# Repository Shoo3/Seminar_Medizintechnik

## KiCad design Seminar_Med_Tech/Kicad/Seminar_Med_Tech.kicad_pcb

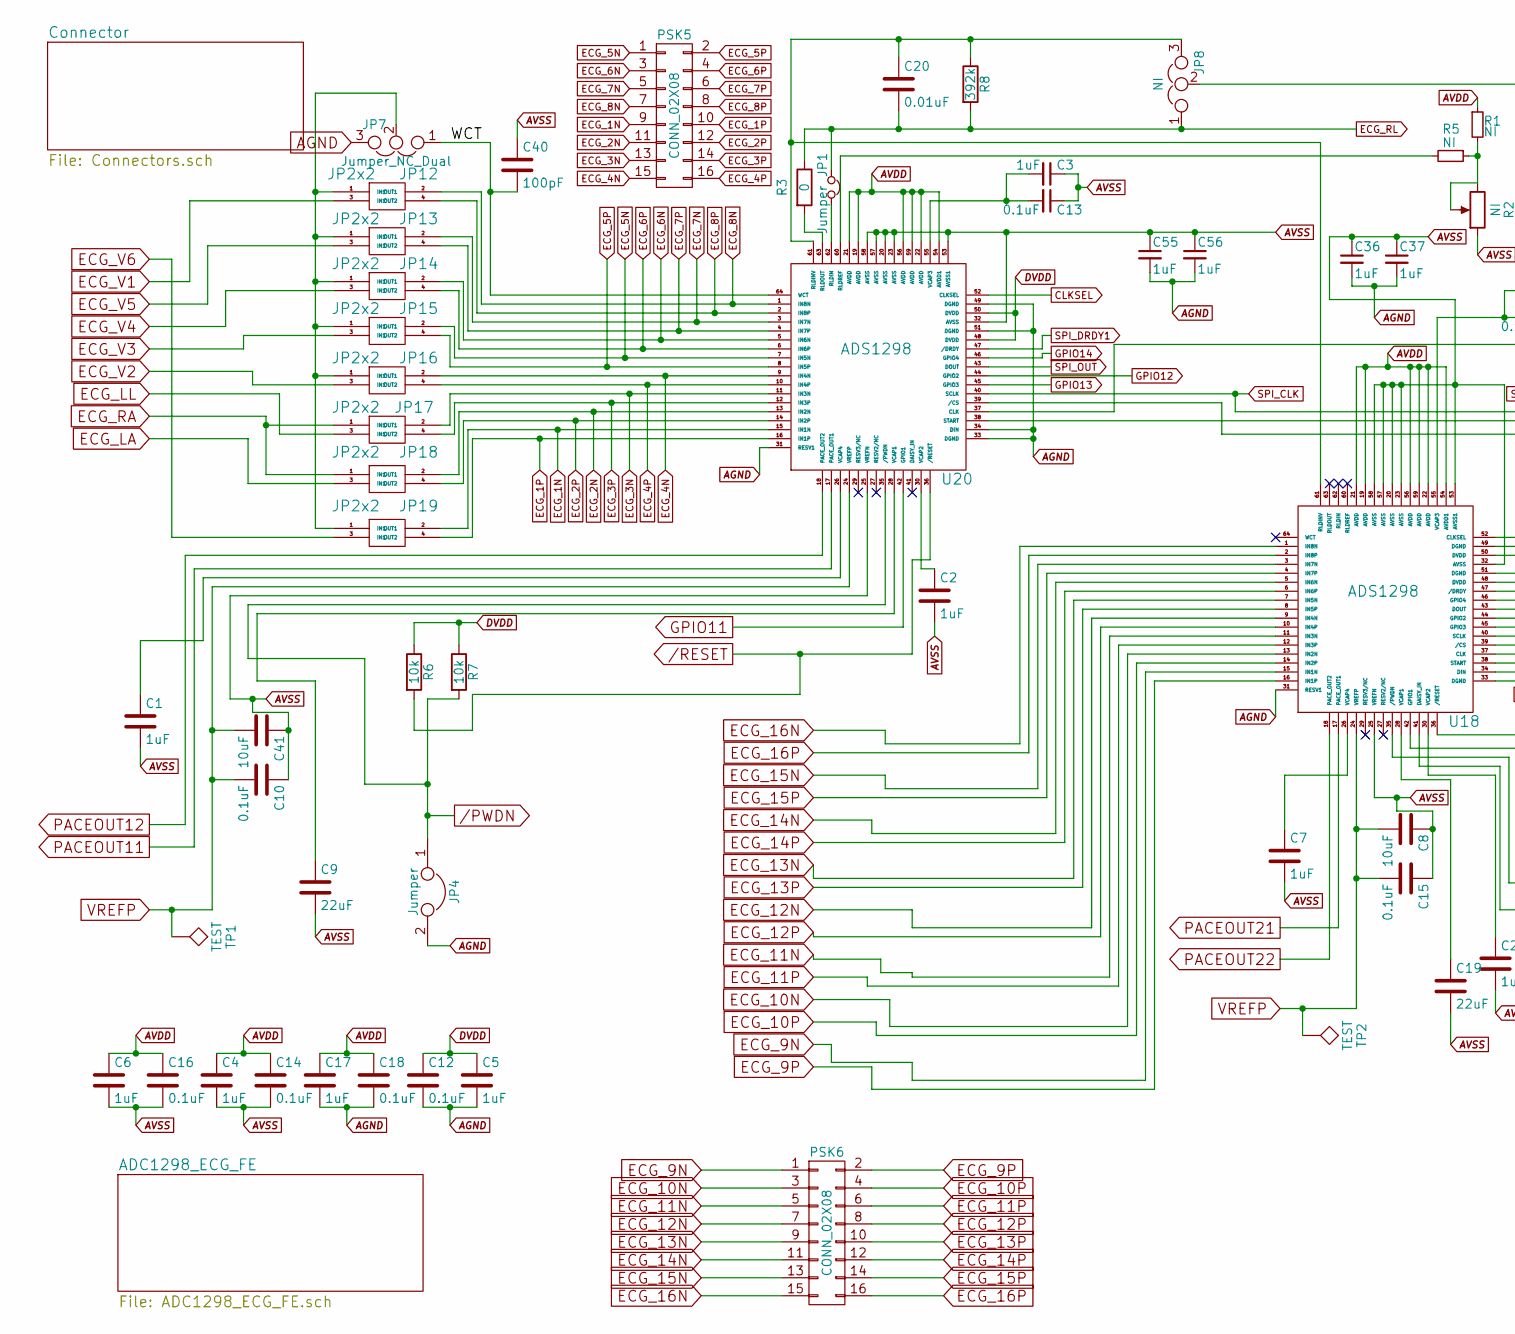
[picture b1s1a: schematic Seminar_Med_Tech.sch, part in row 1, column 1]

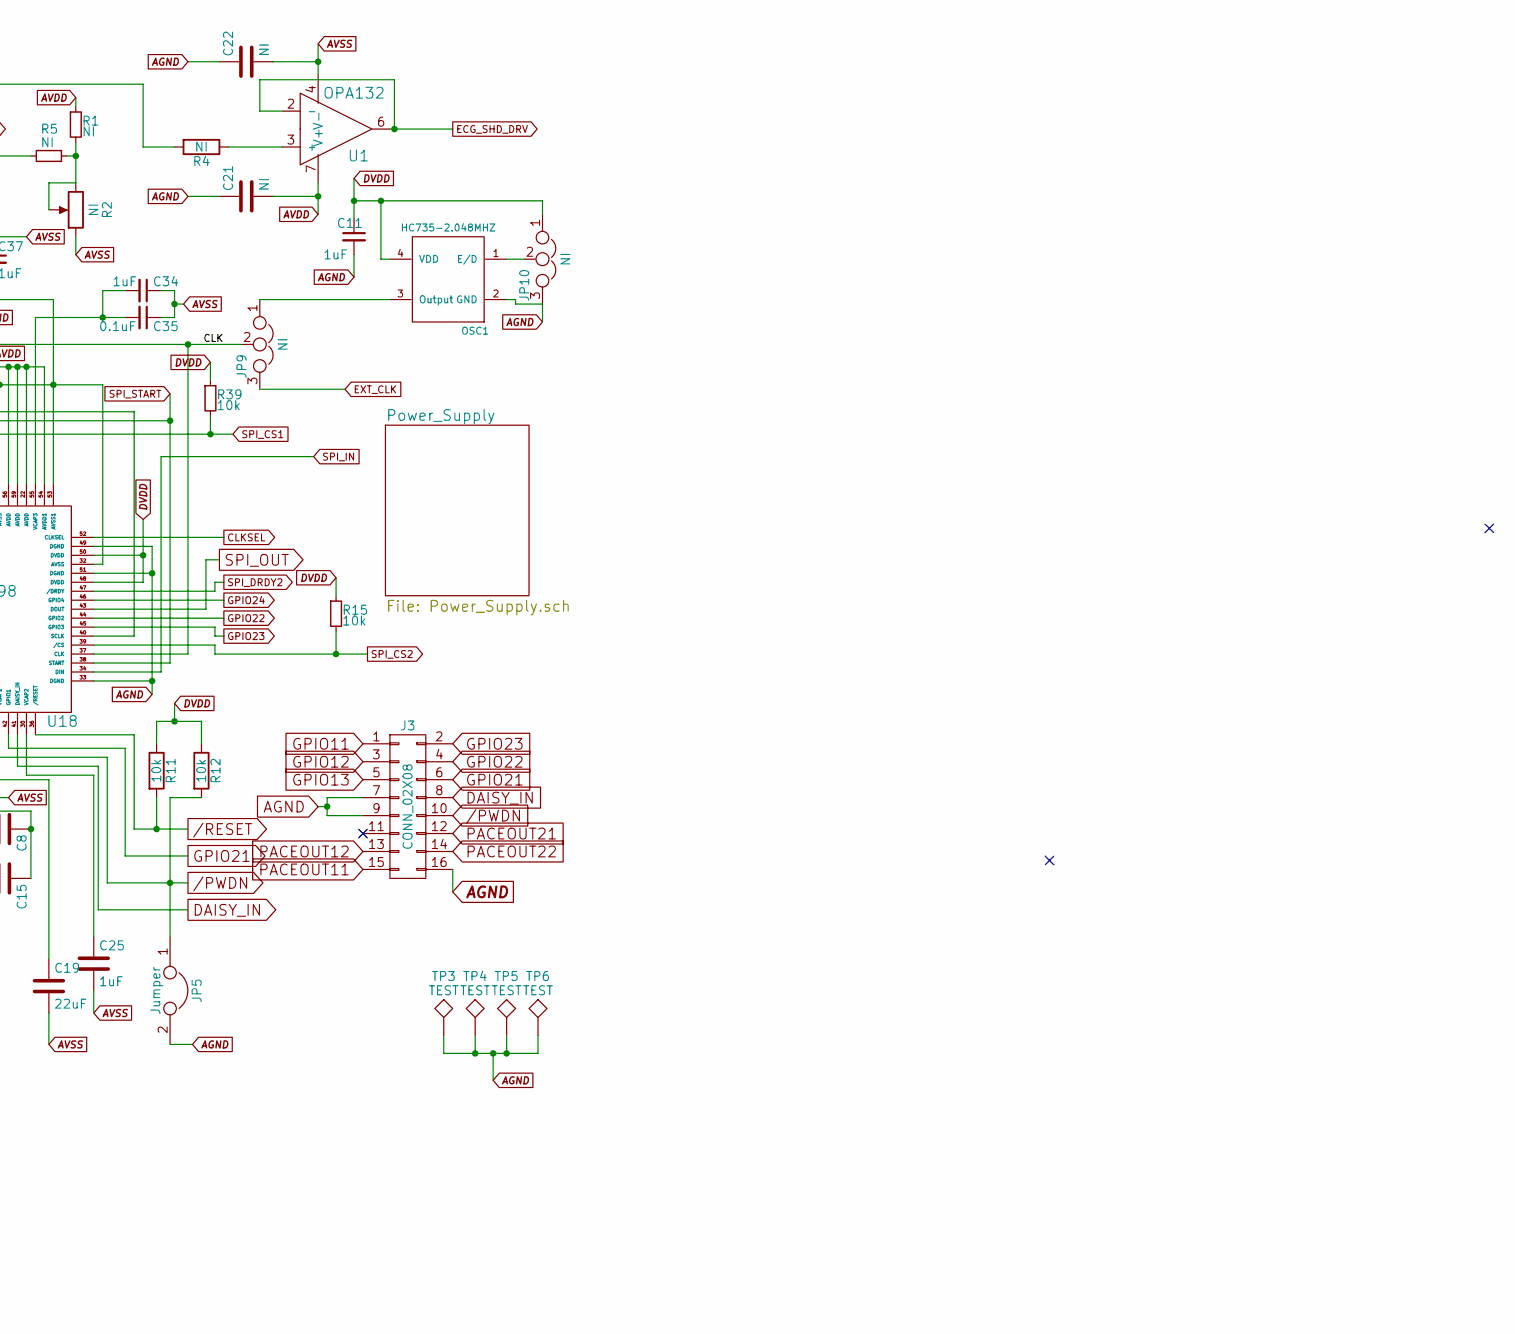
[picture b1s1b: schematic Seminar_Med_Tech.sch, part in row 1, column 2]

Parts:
C1, C2, C3, C4, C5, C6, C7, C11, C17, C25, C34, C36, C37, C55, C56: 1uF; C_1206_HandSoldering
C8, C41: 10uF; C_1206_HandSoldering
C9, C19: 22uF; C_1206_HandSoldering
C10, C12, C13, C14, C15, C16, C18, C35: 0.1uF; C_1206_HandSoldering
C20: 0.01uF; C_1206_HandSoldering
C21, C22: NI; C_1206_HandSoldering
C40: 100pF; C_1206_HandSoldering
J3: CONN_02X08; Pin_Header_Straight_2x08_Pitch2.54mm
JP1, JP4, JP5: Jumper; Jumper1x2
JP7: Jumper_NC_Dual; jumper1x3
JP8, JP9, JP10: NI; jumper1x3
JP12, JP13, JP14, JP15, JP16, JP17, JP18, JP19: JP2x2; Jumper2x2
OSC1: HC735-2.048MHZ; FXO-HC735
PSK5, PSK6: CONN_02X08; Pin_Header_Straight_2x08_Pitch2.54mm
R1, R4, R5: NI; R_0805_HandSoldering
R2: NI; Potentiometer_WirePads_Small
R3: 0; R_0805_HandSoldering
R6, R7, R11, R12, R15, R39: 10k; R_0805_HandSoldering
R8: 392k; R_0805_HandSoldering
TP1, TP2, TP3, TP4, TP5, TP6: TEST; Measurement_Point_Round-TH_Small
U1: OPA132
U18, U20: ADS1298

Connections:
/CLK: JP9.2, U18.37 (CLK), U20.37 (CLK)
/PWDN: J3.10, JP4.1, JP5.1, R7.2, R12.2, U18.35 (/PWDN), U20.35 (/PWDN)
/RESET: R6.2, R11.2, U18.36 (/RESET), U20.36 (/RESET); also elsewhere on the board
/WCT: C40.2, JP7.1, U20.64 (WCT)
AGND: C5.2, C11.2, C12.2, C17.2, C18.2, C21.1, C22.1, C36.2, C37.2, C55.2, C56.2, J3.7, J3.9, J3.16, JP4.2, JP5.2, JP7.3, JP10.3, OSC1.2 (GND), TP3.1, TP4.1, TP5.1, TP6.1, U18.31 (RESV1), U18.33 (DGND), U18.49 (DGND), U18.51 (DGND), U20.31 (RESV1), U20.33 (DGND), U20.34 (DIN), U20.49 (DGND), U20.51 (DGND); also elsewhere on the board
AVDD: C4.1, C6.1, C14.1, C16.1, C17.1, C18.1, C21.2, R1.1, U1.7 (V+), U18.19 (AVDD), U18.21 (AVDD), U18.22 (AVDD), U18.54 (AVDD1), U18.56 (AVDD), U18.59 (AVDD), U20.19 (AVDD), U20.21 (AVDD), U20.22 (AVDD), U20.54 (AVDD1), U20.56 (AVDD), U20.59 (AVDD); also elsewhere on the board
AVSS: C1.2, C2.2, C3.1, C4.2, C6.2, C7.2, C8.1, C9.2, C10.1, C13.1, C14.2, C15.1, C16.2, C19.2, C22.2, C25.2, C34.1, C35.1, C36.1, C37.1, C40.1, C41.1, C55.1, C56.1, R2.1, U1.4 (V-), U18.20 (AVSS), U18.23 (AVSS), U18.25 (VREFN), U18.32 (AVSS), U18.53 (AVSS1), U18.57 (AVSS), U18.58 (AVSS), U20.20 (AVSS), U20.23 (AVSS), U20.25 (VREFN), U20.32 (AVSS), U20.53 (AVSS1), U20.57 (AVSS), U20.58 (AVSS); also elsewhere on the board
CLKSEL: U18.52 (CLKSEL), U20.52 (CLKSEL); also elsewhere on the board
DAISY_IN: J3.8, U18.41 (DAISY_IN)
DVDD: C5.1, C11.1, C12.1, JP10.1, OSC1.4 (VDD), R6.1, R7.1, R11.1, R12.1, R15.1, R39.1, U18.48 (DVDD), U18.50 (DVDD), U20.48 (DVDD), U20.50 (DVDD); also elsewhere on the board
ECG_1N: JP19.2 (OUT1), PSK5.9, U20.15 (IN1N)
ECG_1P: JP19.4 (OUT2), PSK5.10, U20.16 (IN1P)
ECG_2N: JP18.2 (OUT1), PSK5.11, U20.13 (IN2N)
ECG_2P: JP18.4 (OUT2), PSK5.12, U20.14 (IN2P)
ECG_3N: JP17.2 (OUT1), PSK5.13, U20.11 (IN3N)
ECG_3P: JP17.4 (OUT2), PSK5.14, U20.12 (IN3P)
ECG_4N: JP16.2 (OUT1), PSK5.15, U20.9 (IN4N)
ECG_4P: JP16.4 (OUT2), PSK5.16, U20.10 (IN4P)
ECG_5N: JP15.2 (OUT1), PSK5.1, U20.7 (IN5N)
ECG_5P: JP15.4 (OUT2), PSK5.2, U20.8 (IN5P)
ECG_6N: JP14.2 (OUT1), PSK5.3, U20.5 (IN6N)
ECG_6P: JP14.4 (OUT2), PSK5.4, U20.6 (IN6P)
ECG_7N: JP13.2 (OUT1), PSK5.5, U20.3 (IN7N)
ECG_7P: JP13.4 (OUT2), PSK5.6, U20.4 (IN7P)
ECG_8N: JP12.2 (OUT1), PSK5.7, U20.1 (IN8N)
ECG_8P: JP12.4 (OUT2), PSK5.8, U20.2 (IN8P)
ECG_9N: PSK6.1, U18.15 (IN1N)
ECG_9P: PSK6.2, U18.16 (IN1P)
ECG_10N: PSK6.3, U18.13 (IN2N)
ECG_10P: PSK6.4, U18.14 (IN2P)
ECG_11N: PSK6.5, U18.11 (IN3N)
ECG_11P: PSK6.6, U18.12 (IN3P)
ECG_12N: PSK6.7, U18.9 (IN4N)
ECG_12P: PSK6.8, U18.10 (IN4P)
ECG_13N: PSK6.9, U18.7 (IN5N)
ECG_13P: PSK6.10, U18.8 (IN5P)
ECG_14N: PSK6.11, U18.5 (IN6N)
ECG_14P: PSK6.12, U18.6 (IN6P)
ECG_15N: PSK6.13, U18.3 (IN7N)
ECG_15P: PSK6.14, U18.4 (IN7P)
ECG_16N: PSK6.15, U18.1 (IN8N)
ECG_16P: PSK6.16, U18.2 (IN8P)
ECG_LA: JP18.3 (IN1); also elsewhere on the board
ECG_LL: JP17.3 (IN1); also elsewhere on the board
ECG_RA: JP17.1 (IN1), JP18.1 (IN1); also elsewhere on the board
ECG_RL: C20.2, JP1.1, JP8.1, R3.1, R8.2; also elsewhere on the board
ECG_SHD_DRV: U1.2 (-), U1.6; also elsewhere on the board
ECG_V1: JP12.3 (IN1); also elsewhere on the board
ECG_V2: JP16.3 (IN1); also elsewhere on the board
ECG_V3: JP15.3 (IN1); also elsewhere on the board
ECG_V4: JP14.3 (IN1); also elsewhere on the board
ECG_V5: JP13.3 (IN1); also elsewhere on the board
ECG_V6: JP19.3 (IN1); also elsewhere on the board
EXT_CLK: JP9.3; also elsewhere on the board
GPIO11: J3.1, U20.42 (GPIO1)
GPIO12: J3.3, U20.44 (GPIO2)
GPIO13: J3.5, U20.45 (GPIO3)
GPIO14: U20.46 (GPIO4); also elsewhere on the board
GPIO21: J3.6, U18.42 (GPIO1)
GPIO22: J3.4, U18.44 (GPIO2)
GPIO23: J3.2, U18.45 (GPIO3)
GPIO24: U18.46 (GPIO4); also elsewhere on the board
unnamed: C1.1, U20.26 (VCAP4)
unnamed: C2.1, U20.30 (VCAP2)
unnamed: C7.1, U18.26 (VCAP4)
unnamed: C9.1, U20.28 (VCAP1)
unnamed: C3.2, C13.2, U20.55 (VCAP3)
unnamed: C19.1, U18.28 (VCAP1)
unnamed: C20.1, JP8.3, R8.1, U18.61 (RLDINV), U20.61 (RLDINV)
unnamed: C25.1, U18.30 (VCAP2)
unnamed: C34.2, C35.2, U18.55 (VCAP3)
unnamed: JP1.2, U20.62 (RLDIN)
unnamed: JP8.2, R4.2
unnamed: JP9.1, OSC1.3 (Output)
unnamed: JP10.2, OSC1.1 (E/D)
unnamed: JP7.2, JP12.1 (IN1), JP13.1 (IN1), JP14.1 (IN1), JP15.1 (IN1), JP16.1 (IN1), JP19.1 (IN1)
unnamed: R1.2, R2.2, R2.3, R5.1
unnamed: R3.2, U20.63 (RLDOUT)
unnamed: R4.1, U1.3 (+)
unnamed: R5.2, U20.60 (RLDREF)
PACEOUT11: J3.15, U20.17 (PACE_OUT1)
PACEOUT12: J3.13, U20.18 (PACE_OUT2)
PACEOUT21: J3.12, U18.17 (PACE_OUT1)
PACEOUT22: J3.14, U18.18 (PACE_OUT2)
SPI_CLK: U18.40 (SCLK), U20.40 (SCLK); also elsewhere on the board
SPI_CS1: R39.2, U20.39 (/CS); also elsewhere on the board
SPI_CS2: R15.2, U18.39 (/CS); also elsewhere on the board
SPI_DRDY1: U20.47 (/DRDY); also elsewhere on the board
SPI_DRDY2: U18.47 (/DRDY); also elsewhere on the board
SPI_IN: U18.34 (DIN); also elsewhere on the board
SPI_OUT: U18.43 (DOUT), U20.43 (DOUT); also elsewhere on the board
SPI_START: U18.38 (START), U20.38 (START); also elsewhere on the board
VREFP: C8.2, C10.2, C15.2, C41.2, TP1.1, TP2.1, U18.24 (VREFP), U20.24 (VREFP)

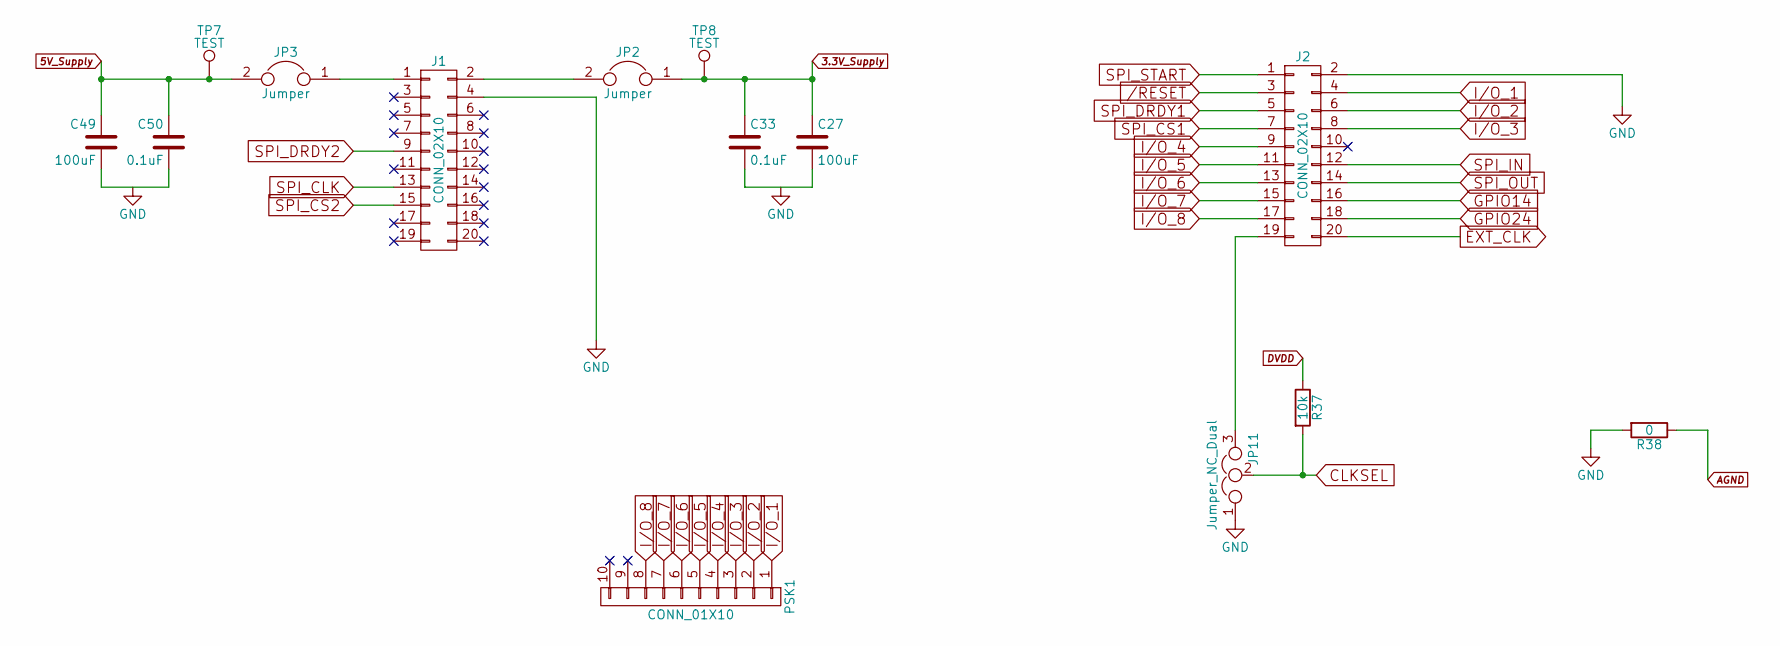
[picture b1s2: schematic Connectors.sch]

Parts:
C27, C49: 100uF; C_1206_HandSoldering
C33, C50: 0.1uF; C_1206_HandSoldering
J1, J2: CONN_02X10; Pin_Header_Straight_2x10_Pitch2.54mm
JP2, JP3: Jumper; Jumper1x2
JP11: Jumper_NC_Dual; jumper1x3
PSK1: CONN_01X10; Pin_Header_Straight_1x10_Pitch2.54mm
R37: 10k; R_0805_HandSoldering
R38: 0; R_0805_HandSoldering
TP7, TP8: TEST; Measurement_Point_Round-TH_Small

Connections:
3.3V_Supply: C27.1, C33.1, JP2.1, TP8.1; also elsewhere on the board
5V_Supply: C49.1, C50.1, JP3.2, TP7.1; also elsewhere on the board
/RESET: J2.3; also elsewhere on the board
AGND: R38.1; also elsewhere on the board
CLKSEL: JP11.2, R37.2; also elsewhere on the board
DVDD: R37.1; also elsewhere on the board
EXT_CLK: J2.20; also elsewhere on the board
GPIO14: J2.16; also elsewhere on the board
GPIO24: J2.18; also elsewhere on the board
I/O_1: J2.4, PSK1.1
I/O_2: J2.6, PSK1.2
I/O_3: J2.8, PSK1.3
I/O_4: J2.9, PSK1.4
I/O_5: J2.11, PSK1.5
I/O_6: J2.13, PSK1.6
I/O_7: J2.15, PSK1.7
I/O_8: J2.17, PSK1.8
unnamed: J2.19, JP11.3
SPI_CLK: J1.13; also elsewhere on the board
SPI_CS1: J2.7; also elsewhere on the board
SPI_CS2: J1.15; also elsewhere on the board
SPI_DRDY1: J2.5; also elsewhere on the board
SPI_DRDY2: J1.9; also elsewhere on the board
SPI_IN: J2.12; also elsewhere on the board
SPI_OUT: J2.14; also elsewhere on the board
SPI_START: J2.1; also elsewhere on the board

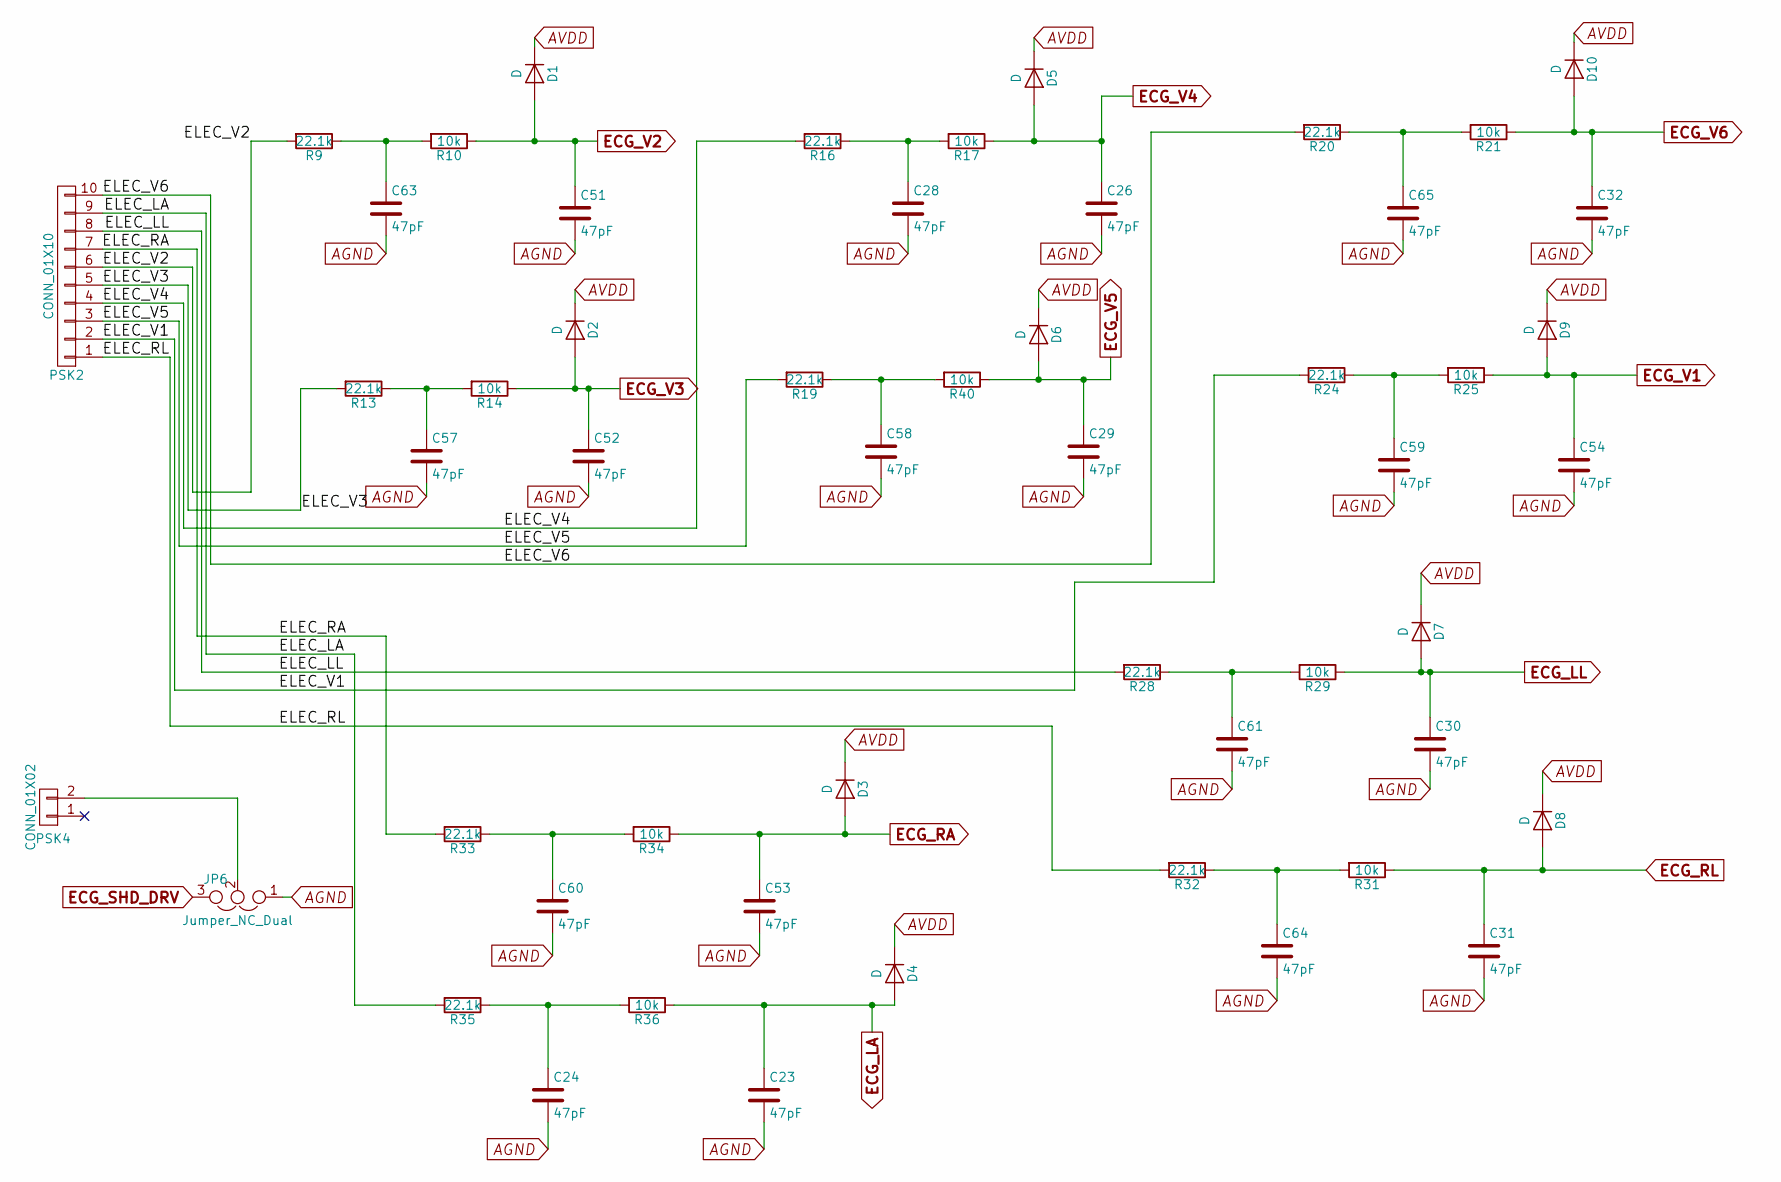
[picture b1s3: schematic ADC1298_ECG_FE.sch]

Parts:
C23, C24, C26, C28, C29, C30, C31, C32, C51, C52, C53, C54, C57, C58, C59, C60, C61, C63, C64, C65: 47pF; C_1206_HandSoldering
D1, D2, D3, D4, D5, D6, D7, D8, D9, D10: D; D_SOD-123
JP6: Jumper_NC_Dual; jumper1x3
PSK2: CONN_01X10; Pin_Header_Straight_1x10_Pitch2.54mm
PSK4: CONN_01X02; Pin_Header_Straight_1x02_Pitch2.54mm
R9, R13, R16, R19, R20, R24, R28, R32, R33, R35: 22.1k; R_0805_HandSoldering
R10, R14, R17, R21, R25, R29, R31, R34, R36, R40: 10k; R_0805_HandSoldering

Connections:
/ADC1298_ECG_FE/ELEC_LA: PSK2.9, R35.2
/ADC1298_ECG_FE/ELEC_LL: PSK2.8, R28.2
/ADC1298_ECG_FE/ELEC_RA: PSK2.7, R33.2
/ADC1298_ECG_FE/ELEC_RL: PSK2.1, R32.2
/ADC1298_ECG_FE/ELEC_V1: PSK2.2, R24.2
/ADC1298_ECG_FE/ELEC_V2: PSK2.6, R9.2
/ADC1298_ECG_FE/ELEC_V3: PSK2.5, R13.2
/ADC1298_ECG_FE/ELEC_V4: PSK2.4, R16.2
/ADC1298_ECG_FE/ELEC_V5: PSK2.3, R19.2
/ADC1298_ECG_FE/ELEC_V6: PSK2.10, R20.2
AGND: C23.2, C24.2, C26.2, C28.2, C29.2, C30.2, C31.2, C32.2, C51.2, C52.2, C53.2, C54.2, C57.2, C58.2, C59.2, C60.2, C61.2, C63.2, C64.2, C65.2, JP6.1; also elsewhere on the board
AVDD: D1.1 (K), D2.1 (K), D3.1 (K), D4.1 (K), D5.1 (K), D6.1 (K), D7.1 (K), D8.1 (K), D9.1 (K), D10.1 (K); also elsewhere on the board
ECG_LA: C23.1, D4.2 (A), R36.1; also elsewhere on the board
ECG_LL: C30.1, D7.2 (A), R29.1; also elsewhere on the board
ECG_RA: C53.1, D3.2 (A), R34.1; also elsewhere on the board
ECG_RL: C31.1, D8.2 (A), R31.1; also elsewhere on the board
ECG_SHD_DRV: JP6.3; also elsewhere on the board
ECG_V1: C54.1, D9.2 (A), R25.1; also elsewhere on the board
ECG_V2: C51.1, D1.2 (A), R10.1; also elsewhere on the board
ECG_V3: C52.1, D2.2 (A), R14.1; also elsewhere on the board
ECG_V4: C26.1, D5.2 (A), R17.1; also elsewhere on the board
ECG_V5: C29.1, D6.2 (A), R40.1; also elsewhere on the board
ECG_V6: C32.1, D10.2 (A), R21.1; also elsewhere on the board
unnamed: C24.1, R35.1, R36.2
unnamed: C28.1, R16.1, R17.2
unnamed: C57.1, R13.1, R14.2
unnamed: C58.1, R19.1, R40.2
unnamed: C59.1, R24.1, R25.2
unnamed: C60.1, R33.1, R34.2
unnamed: C61.1, R28.1, R29.2
unnamed: C63.1, R9.1, R10.2
unnamed: C64.1, R31.2, R32.1
unnamed: C65.1, R20.1, R21.2
unnamed: JP6.2, PSK4.2

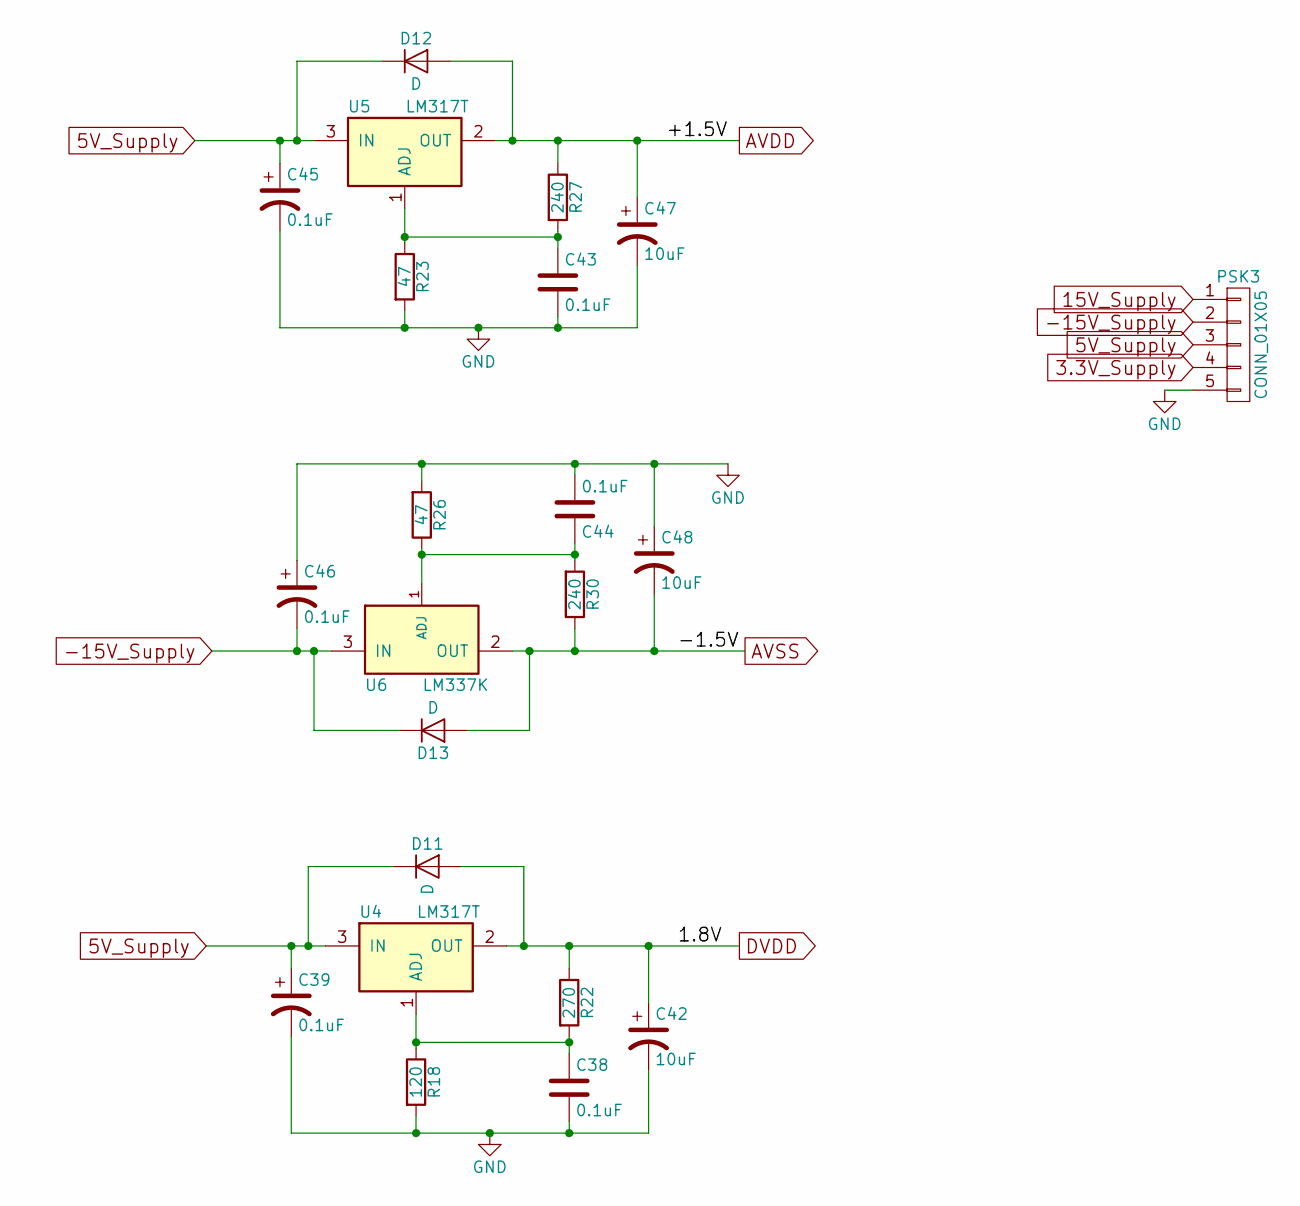
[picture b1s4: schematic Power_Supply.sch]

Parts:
C38, C43, C44: 0.1uF; C_1206_HandSoldering
C39, C45, C46: 0.1uF; 4mmx5,5mmSMDElec
C42, C47, C48: 10uF; 4mmx5,5mmSMDElec10uf
D11, D12, D13: D; D_SOD-123
PSK3: CONN_01X05; Pin_Header_Straight_1x05_Pitch2.54mm
R18: 120; R_0805_HandSoldering
R22: 270; R_0805_HandSoldering
R23, R26: 47; R_0805_HandSoldering
R27, R30: 240; R_0805_HandSoldering
U4, U5: LM317T; LM317
U6: LM337K; LM317

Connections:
3.3V_Supply: PSK3.4; also elsewhere on the board
5V_Supply: C39.1, C45.1, D11.1 (K), D12.1 (K), PSK3.3, U4.3 (IN), U5.3 (IN); also elsewhere on the board
15V_Supply: PSK3.1
-15V_Supply: C46.2, D13.1 (K), PSK3.2, U6.3 (IN)
AVDD: C47.1, D12.2 (A), R27.1, U5.2 (OUT); also elsewhere on the board
AVSS: C48.2, D13.2 (A), R30.1, U6.2 (OUT); also elsewhere on the board
DVDD: C42.1, D11.2 (A), R22.1, U4.2 (OUT); also elsewhere on the board
unnamed: C38.1, R18.1, R22.2, U4.1 (ADJ)
unnamed: C43.1, R23.1, R27.2, U5.1 (ADJ)
unnamed: C44.1, R26.1, R30.2, U6.1 (ADJ)

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
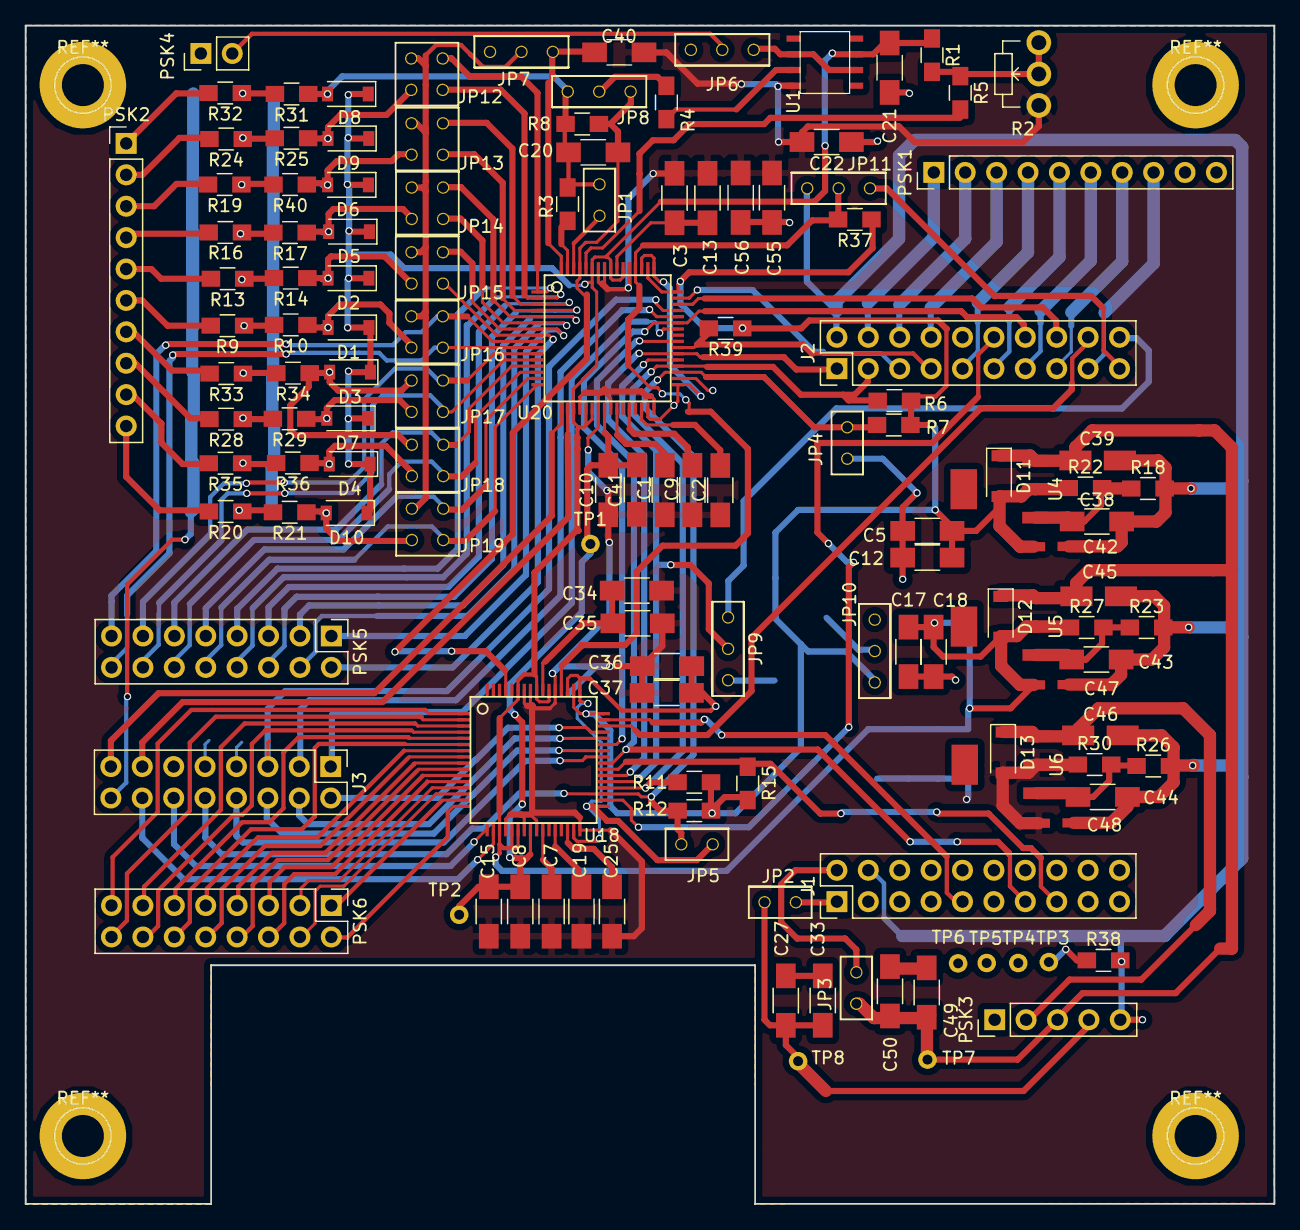
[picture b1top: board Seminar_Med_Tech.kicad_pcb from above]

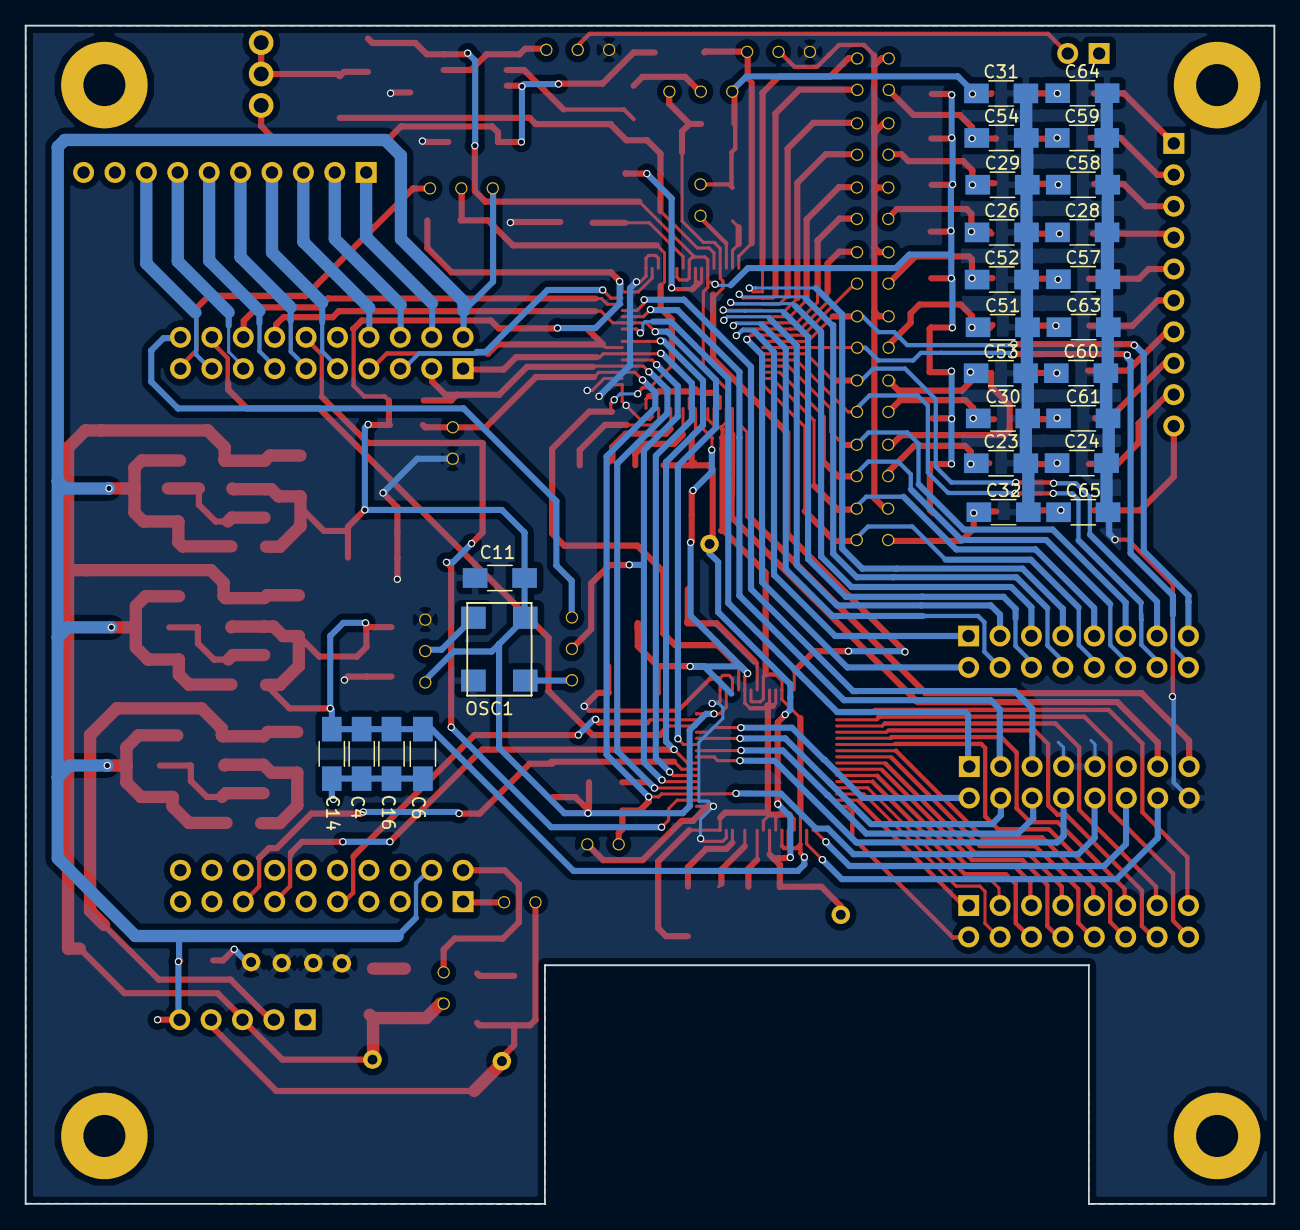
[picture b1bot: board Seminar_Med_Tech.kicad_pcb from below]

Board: 2 copper layers, 101.0 x 95.3 mm, 160 parts (26 on the bottom side), 134 nets.

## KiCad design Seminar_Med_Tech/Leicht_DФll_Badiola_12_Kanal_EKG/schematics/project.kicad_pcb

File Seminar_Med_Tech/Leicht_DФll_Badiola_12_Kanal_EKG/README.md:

Ziel des Projekt ist es, die empfangen Daten des ECG an Matlab zu
übertragen und auszuwerten.

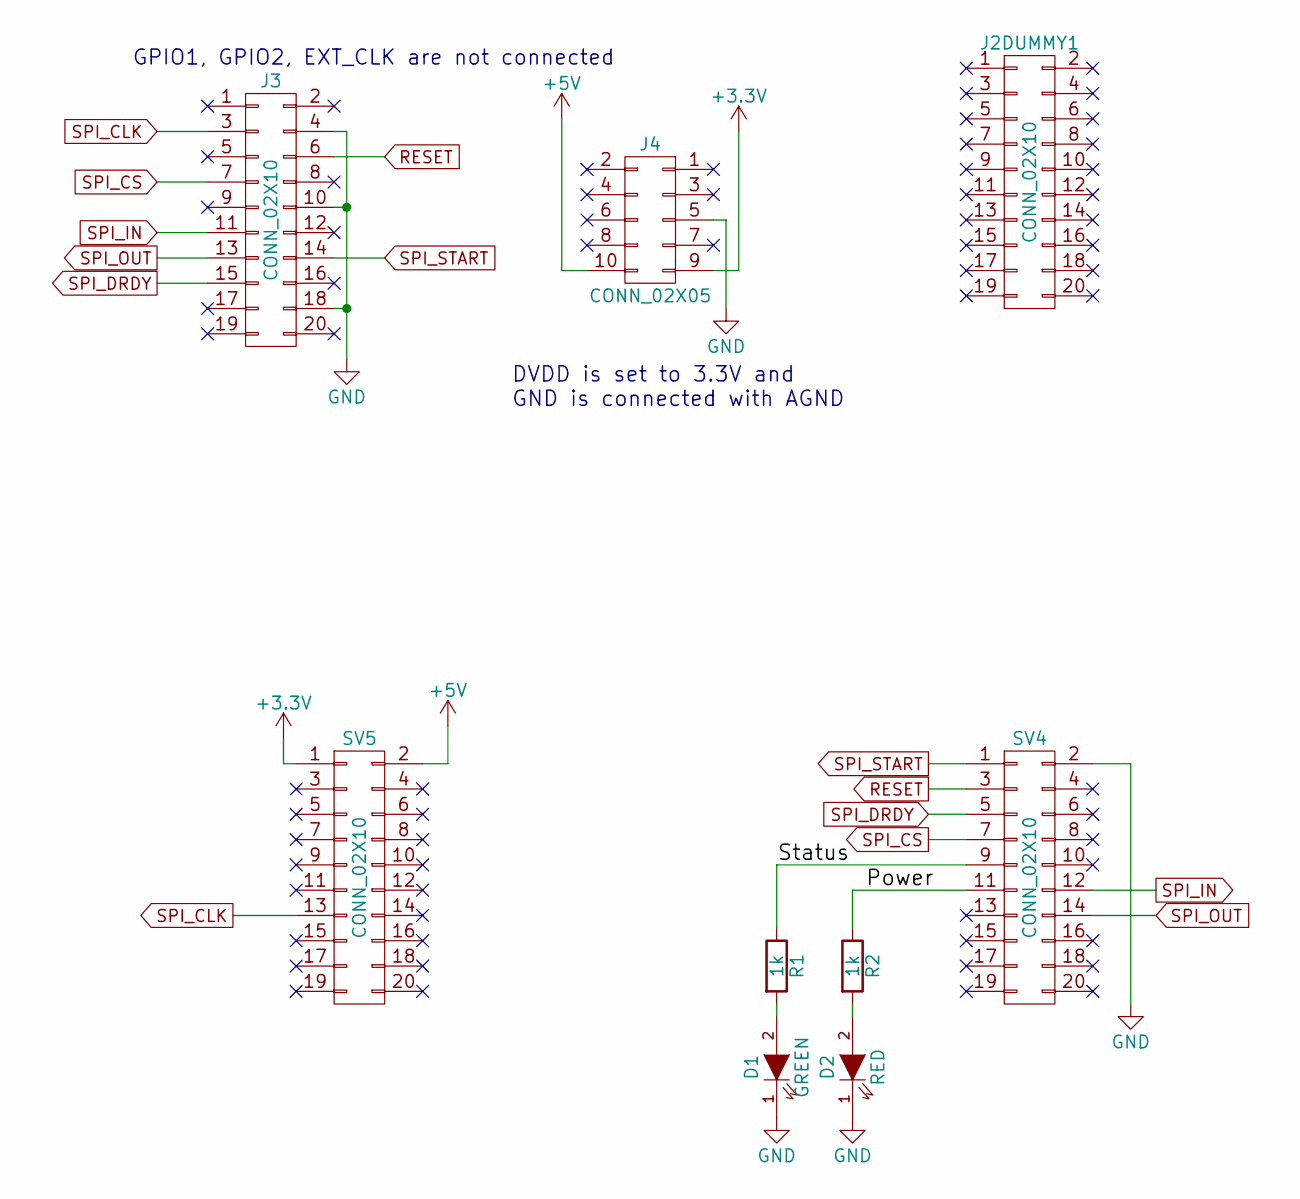
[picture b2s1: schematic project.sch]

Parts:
D1: GREEN; LED-5MM
D2: RED; LED-5MM
J2DUMMY1, J3: CONN_02X10; Pin_Header_Straight_2x10_Pitch2.54mm
J4: CONN_02X05; Pin_Header_Straight_2x05_Pitch2.54mm
R1, R2: 1k; Resistor_Horizontal_RM10mm
SV4, SV5: CONN_02X10; Socket_Strip_Straight_2x10

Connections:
+3V3: J4.9, SV5.1
+5V: J4.10, SV5.2
/Power: R2.1, SV4.11
/Status: R1.1, SV4.9
GND: D1.1 (K), D2.1 (K), J3.4, J3.10, J3.18, J4.5, SV4.2
unnamed: D1.2 (A), R1.2
unnamed: D2.2 (A), R2.2
RESET: J3.6, SV4.3
SPI_CLK: J3.3, SV5.13
SPI_CS: J3.7, SV4.7
SPI_DRDY: J3.15, SV4.5
SPI_IN: J3.11, SV4.12
SPI_OUT: J3.13, SV4.14
SPI_START: J3.14, SV4.1

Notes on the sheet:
DVDD is set to 3.3V and GND is connected with AGND
GPIO1, GPIO2, EXT_CLK are not connected

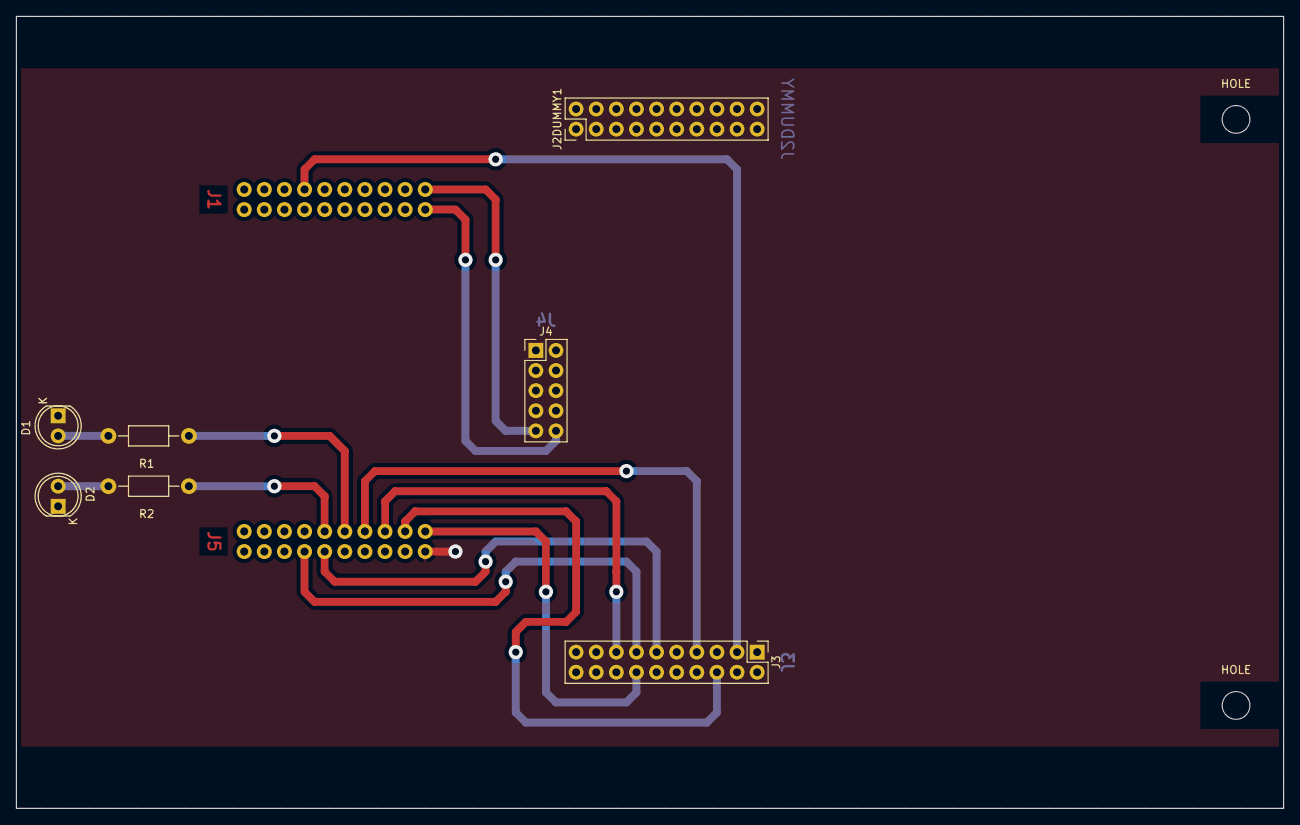
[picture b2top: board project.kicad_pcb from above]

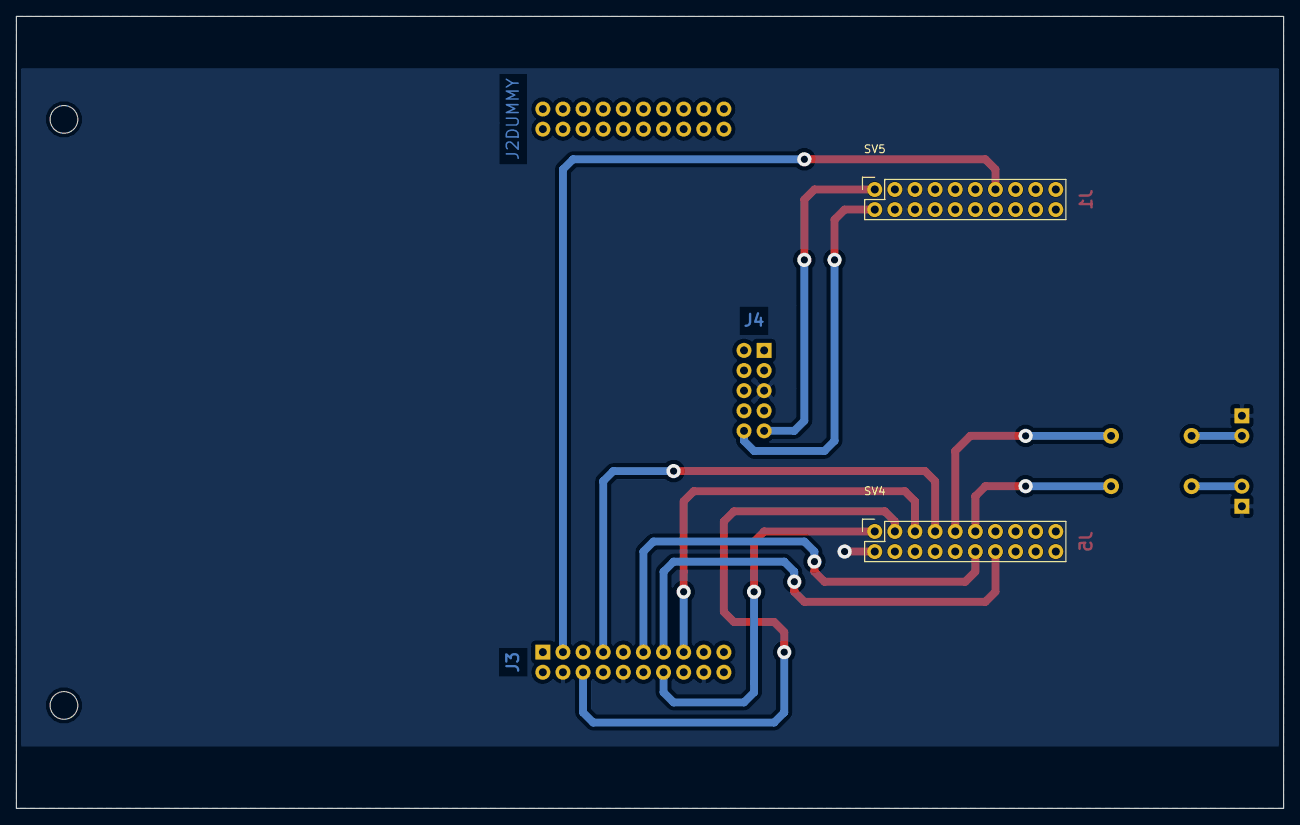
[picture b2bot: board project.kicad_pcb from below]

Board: 2 copper layers, 160.0 x 100.0 mm, 11 parts (2 on the bottom side), 14 nets.

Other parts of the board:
HOLE: MountingHole_3.5mm
HOLE#2: MountingHole_3.5mm
